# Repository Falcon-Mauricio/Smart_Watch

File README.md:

# Smart_Watch
Repositorio dedicado al desarrollo de un reloj inteligente capaz de recibir información mediante conexión wifi

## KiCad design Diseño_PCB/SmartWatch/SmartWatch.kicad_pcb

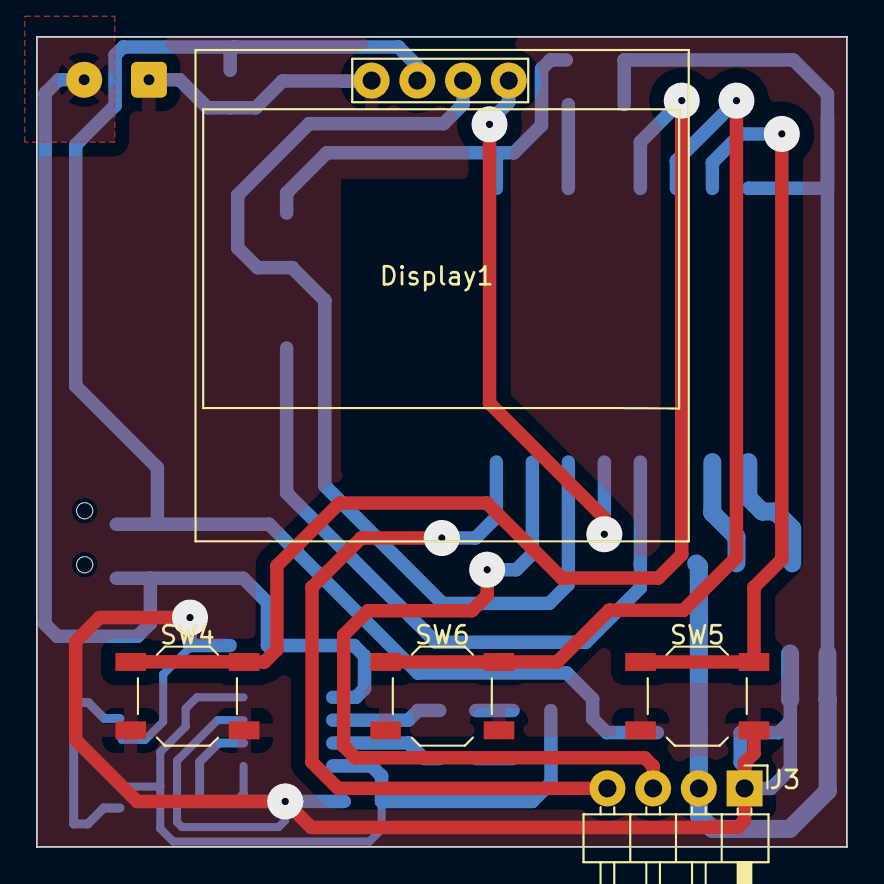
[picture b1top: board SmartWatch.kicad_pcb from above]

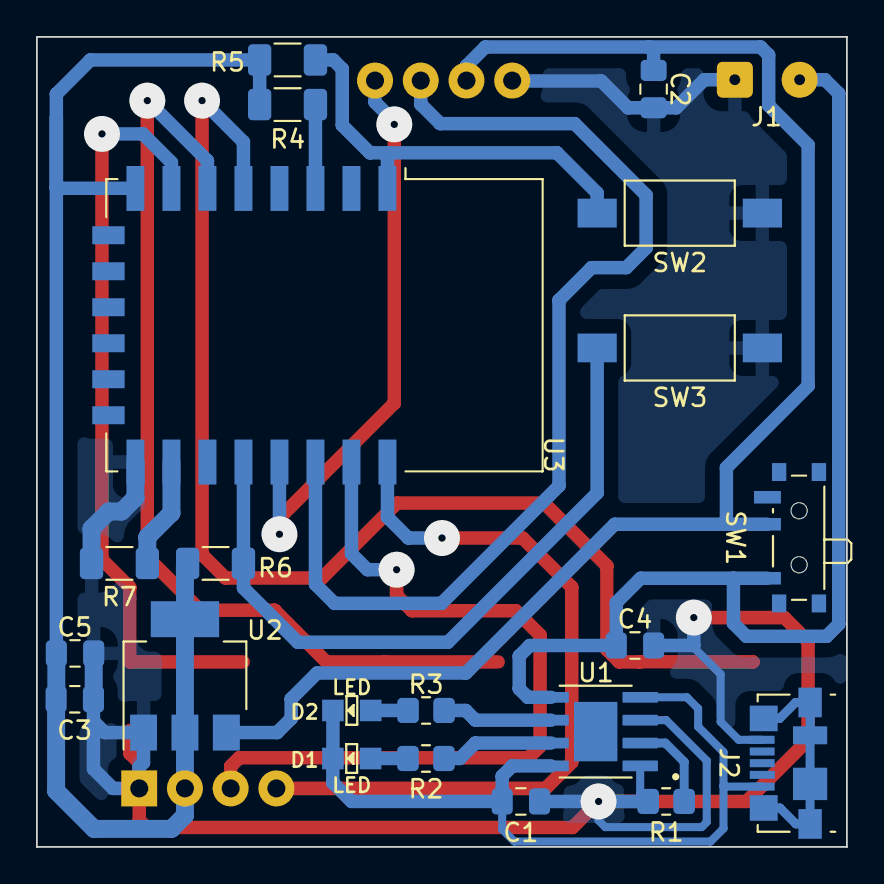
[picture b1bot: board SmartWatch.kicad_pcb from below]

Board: 2 copper layers, 45.0 x 45.0 mm, 27 parts (22 on the bottom side), 21 nets.

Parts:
C1, C4, C5: 10uF; C_0805_2012Metric_Pad1.18x1.45mm_HandSolder
C2, C3: 1uF; C_0805_2012Metric_Pad1.18x1.45mm_HandSolder
D1, D2: LED; Led_0805
Display1: SSD1306-SSD1306-128x64_OLED; 128x64OLED
J1: Input_BAT; SolderWire-0.1sqmm_1x02_P3.6mm_D0.4mm_OD1mm
J2: USB_B_Micro; USB_Micro-B_Molex_47346-0001
J3: FTDI; PinHeader_1x04_P2.54mm_Horizontal
R1: 1K2; R_0805_2012Metric_Pad1.20x1.40mm_HandSolder
R2, R3: 1K; R_0805_2012Metric_Pad1.20x1.40mm_HandSolder
R4, R5, R6, R7: 10K; R_1206_3216Metric_Pad1.30x1.75mm_HandSolder
SW1: SW_SPST; SW_SPDT_PCM12
SW2, SW3: SW_Push; SW_SPST_FSMSM
SW4, SW5, SW6: SW_Push_Dual; SW_SPST_TL3342
U1: TP4056; SOP127P600X175-9N
U2: AMS1117-3.3; SOT-223-3_TabPin2
U3: ESP-12F; ESP-12E

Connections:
+3.3V: C3.1, C5.2, J3.2, R4.1, R5.1, R6.1, U2.2 (VO), U3.8 (VCC)
/Rx: J3.3, U3.21 (GPIO3/RXD)
/SCL: Display1.3 (SCL), U3.20 (GPIO5)
/SDA: Display1.4 (SDA), U3.19 (GPIO4)
/Tx: J3.4, U3.22 (GPIO1/TXD)
/VBAT: C4.1, J1.2, SW1.1 (A), U1.5 (BAT)
/VCC_OLED: C2.1, Display1.2 (VCC), SW1.2 (B), U2.3 (VI)
GND: C1.1, C2.2, C3.2, C4.2, C5.1, Display1.1 (GND), J1.1, J2.5 (GND), J3.1, R1.1, R7.2, SW2.1, SW3.2, SW4.1, SW5.1, SW6.1, U1.1 (TEMP), U1.3 (GND), U2.1 (GND), U3.15 (GND)
unnamed: C1.2, D1.2 (A), D2.2 (A), J2.1 (VBUS), U1.4 (VCC), U1.8 (CE)
unnamed: D1.1 (K), R2.2
unnamed: D2.1 (K), R3.2
unnamed: R1.2, U1.2 (PROG)
unnamed: R2.1, U1.7 (~CHRG)
unnamed: R3.1, U1.6 (~STDBY)
unnamed: R4.2, U3.3 (EN)
unnamed: R6.2, SW3.1, U3.18 (GPIO0)
unnamed: SW6.2, U3.6 (GPIO12)
unnamed: SW5.2, U3.7 (GPIO13)
unnamed: SW4.2, U3.5 (GPIO14)
unnamed: R7.1, U3.16 (GPIO15)
unnamed: R5.2, SW2.2, U3.1 (~RST)

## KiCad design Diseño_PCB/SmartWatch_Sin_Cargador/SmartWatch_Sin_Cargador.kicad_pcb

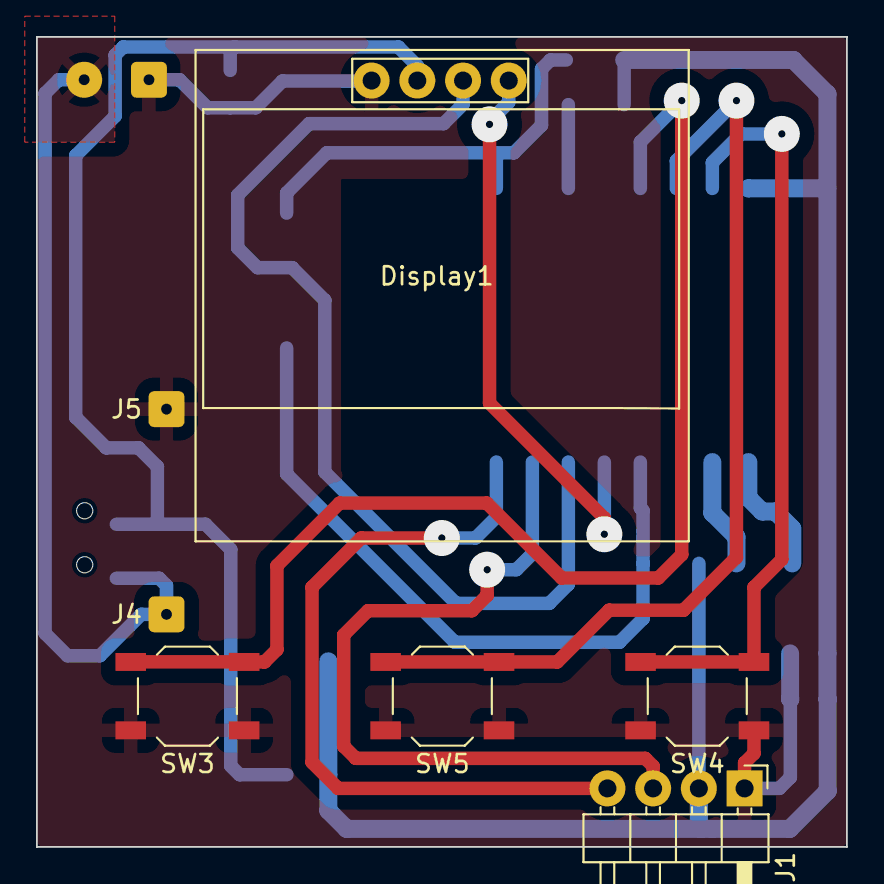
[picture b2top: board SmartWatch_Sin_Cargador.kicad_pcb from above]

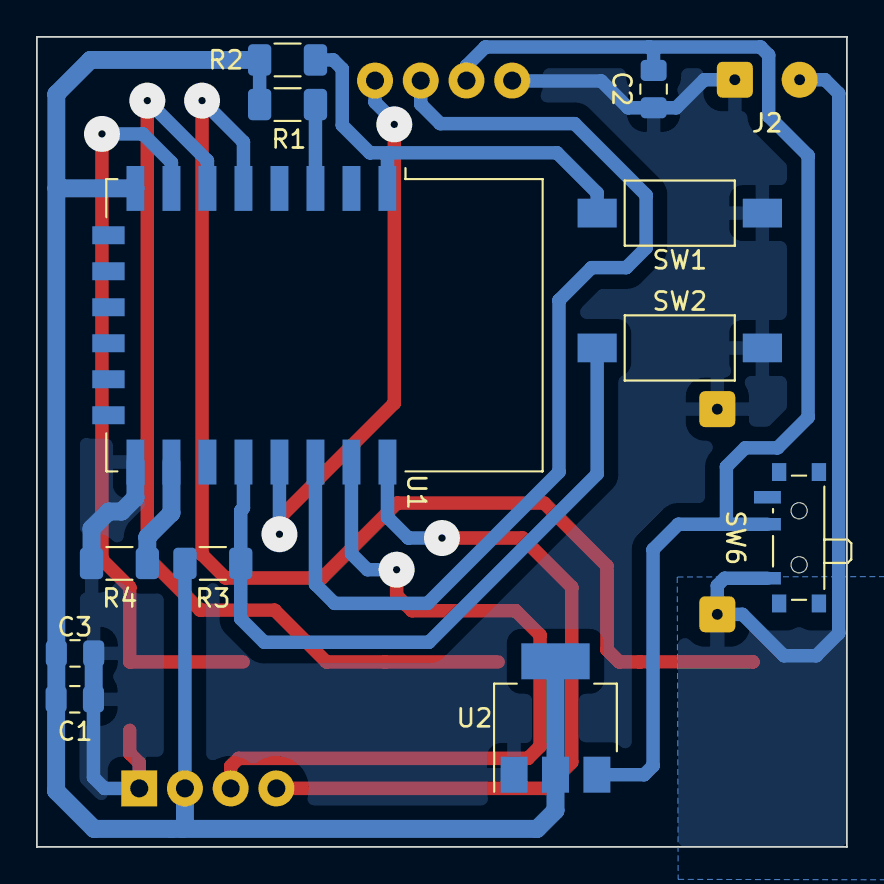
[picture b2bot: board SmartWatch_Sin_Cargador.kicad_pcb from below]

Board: 2 copper layers, 45.0 x 45.0 mm, 20 parts (13 on the bottom side), 15 nets.

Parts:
C1: 10uF; C_0805_2012Metric_Pad1.18x1.45mm_HandSolder
C2, C3: 1uF; C_0805_2012Metric_Pad1.18x1.45mm_HandSolder
Display1: SSD1306-SSD1306-128x64_OLED; 128x64OLED
J1: FTDI; PinHeader_1x04_P2.54mm_Horizontal
J2: Input_BAT; SolderWire-0.1sqmm_1x02_P3.6mm_D0.4mm_OD1mm
J4: Input_Charger++; SolderWire-0.1sqmm_1x01_D0.4mm_OD1mm
J5: Input_Charger--; SolderWire-0.1sqmm_1x01_D0.4mm_OD1mm
R1, R2, R3, R4: 10K; R_1206_3216Metric_Pad1.30x1.75mm_HandSolder
SW1, SW2: SW_Push; SW_SPST_FSMSM
SW3, SW4, SW5: SW_Push_Dual; SW_SPST_TL3342
SW6: SW_SPST; SW_SPDT_PCM12
U1: ESP-12F; ESP-12E
U2: AMS1117-3.3; SOT-223-3_TabPin2

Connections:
+3.3V: C1.2, C3.1, J1.2, R1.1, R2.1, R3.1, U1.8 (VCC), U2.2 (VO)
/Rx: J1.3, U1.21 (GPIO3/RXD)
/SCL: Display1.3 (SCL), U1.20 (GPIO5)
/SDA: Display1.4 (SDA), U1.19 (GPIO4)
/Tx: J1.4, U1.22 (GPIO1/TXD)
/VBAT: J2.2, J4.1, SW6.1 (A)
/VCC_OLED: C2.1, Display1.2 (VCC), SW6.2 (B), U2.3 (VI)
GND: C1.1, C2.2, C3.2, Display1.1 (GND), J1.1, J2.1, J5.1, R4.2, SW1.1, SW2.2, SW3.1, SW4.1, SW5.1, U1.15 (GND), U2.1 (GND)
unnamed: R1.2, U1.3 (EN)
unnamed: R3.2, SW2.1, U1.18 (GPIO0)
unnamed: SW5.2, U1.6 (GPIO12)
unnamed: SW4.2, U1.7 (GPIO13)
unnamed: SW3.2, U1.5 (GPIO14)
unnamed: R4.1, U1.16 (GPIO15)
unnamed: R2.2, SW1.2, U1.1 (~RST)

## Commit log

2023-05-16 Agregue los PCB's del smartwatch y actualice la version beta
2023-05-16 Actualice un SCH
2023-05-17 Cree las carpetas de diseño 3D y actuaice el PCB del que no lleva cargador
2023-05-25 Actualizacion del PCB final
2023-05-25 Eliminacion de .rar
2023-06-05 Arreglo PCB, Creacion de la carcasa 3D
2023-06-05 Arreglo PCB
2023-06-05 Detalles modelo 3D
